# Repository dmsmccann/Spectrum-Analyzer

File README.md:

# W7ZOI Spectrum Analyzer

## KiCad Implementation with modifications by Andy McCann KA3KAF and Doug McCann KA3KAG

## Overview

This repository contains a complete KiCad implementation of the famous W7ZOI Spectrum Analyzer design, originally published in QST magazine. The W7ZOI spectrum analyzer is a well-regarded amateur radio test instrument design that provides a cost-effective solution for RF spectrum analysis.

## Project Description

The W7ZOI Spectrum Analyzer is a superheterodyne spectrum analyzer designed for amateur radio applications. It provides frequency analysis capabilities across the HF and VHF bands, making it an invaluable tool for antenna analysis, filter characterization, and general RF measurements.

### Key Features

- **Frequency Range**: Covers HF through VHF bands
- **Modular Design**: Hierarchical schematic organization for easy understanding and modification
- **Complete Implementation**: Includes all necessary subsystems:
  - VCO and 1st Mixer
  - 110 MHz / 7 MHz Filter sections
  - IF and Log Amplifier
  - 2nd Mixer and 2nd LO
  - Resolution Filters
  - Timebase circuitry
  - 15V Power Supply
  - 2dB Divider
  - 70 MHz Low-pass Filter

## Repository Structure

```text
├── hierarchical-schematic/     # Main hierarchical schematic files
├── 110mhz/                    # 110 MHz filter module
├── 15v-supply/                # Power supply module
├── 2db-div/                   # 2dB divider module
├── 2ndmixer-2ndlo/           # 2nd mixer and LO module
├── 70mhz-lpf/                # 70 MHz low-pass filter
├── 7mhz-crystal-oscillator/  # 7 MHz crystal oscillator
├── if-and-log-amp/           # IF and log amplifier
├── resolution-filters/        # Resolution filter bank
├── timebase/                 # Timebase generation
├── tracking-generator/        # Tracking generator module
├── vco-1stmixer/             # VCO and 1st mixer
├── literature/               # Reference documentation and articles
├── images/                   # Project images and diagrams
└── experimental-data/        # Test data and measurements
```

## Hardware Modules

### Core RF Path

- **VCO and 1st Mixer**: Frequency conversion front-end
- **110 MHz Filter**: First IF filtering
- **7 MHz Crystal Oscillator**: Local oscillator reference
- **2nd Mixer and LO**: Second frequency conversion
- **IF and Log Amplifier**: Signal conditioning and logarithmic response

### Support Circuits

- **15V Power Supply**: Clean, regulated power for all modules
- **Resolution Filters**: Selectable bandwidth filters
- **70 MHz Low-pass Filter**: Anti-aliasing and spurious suppression
- **2dB Divider**: Signal distribution
- **Timebase**: Sweep generation and timing

### Optional Modules

- **Tracking Generator**: Signal source for swept measurements
- **Two-tone Test**: Distortion analysis capability

## Documentation

The `literature/` directory contains extensive reference material including:

- Original QST articles (September 1998, November 1999, June 2001)
- Construction notes and updates
- Filter design references
- Technical papers on spectrum analysis
- Modification and improvement documentation

## Getting Started

### Prerequisites

- KiCad 6.0 or later
- Basic understanding of RF circuit design
- Amateur radio license (for legal operation)

### Opening the Project

1. Clone this repository
2. Open KiCad
3. Load the main project file: `hierarchical-schematic/W7ZOI Spectrum Analyzer.kicad_pro`

### Project Files

- **Schematic**: Hierarchical design with individual module schematics
- **PCB Layout**: Complete board layout for professional fabrication
- **3D Models**: Custom component models for visualization
- **BOM**: Bill of materials with part specifications

## Modifications and Improvements

This implementation includes several improvements over the original design:

- Updated component selections for current availability
- Improved PCB layout with better ground planes
- Enhanced power supply regulation
- Modernized connector choices
- Detailed silkscreen labeling

## Building the Analyzer

Refer to the documentation in the `literature/` directory for detailed construction information. The original QST articles provide comprehensive building instructions, alignment procedures, and performance specifications.

## Contributing

Contributions are welcome! Please feel free to submit issues, improvements, or additional documentation. When contributing:

1. Follow KiCad best practices for schematic and PCB design
2. Document any changes thoroughly
3. Test modifications before submitting
4. Update relevant documentation

## License

This project is based on the original W7ZOI design published in QST magazine. Please respect copyright and amateur radio regulations in your use of these designs.

## Authors and Acknowledgments

- **Original Design**: Wes Hayward (W7ZOI) and Terry White (VE3DTE)
- **KiCad Implementation**: Andy McCann (KA3KAF) and Doug McCann (KA3KAG)
- **Published in**: QST Magazine, September 1998 and subsequent articles

## References

- QST Magazine, September 1998: "A Spectrum Analyzer for the Radio Amateur"
- QST Magazine, November 1999: Part 2 and updates
- QST Magazine, June 2001: Additional modifications and tracking generator
- Various technical papers in the `literature/` directory

---

*This is an amateur radio project intended for educational and experimental use. Please ensure compliance with your local amateur radio regulations.*

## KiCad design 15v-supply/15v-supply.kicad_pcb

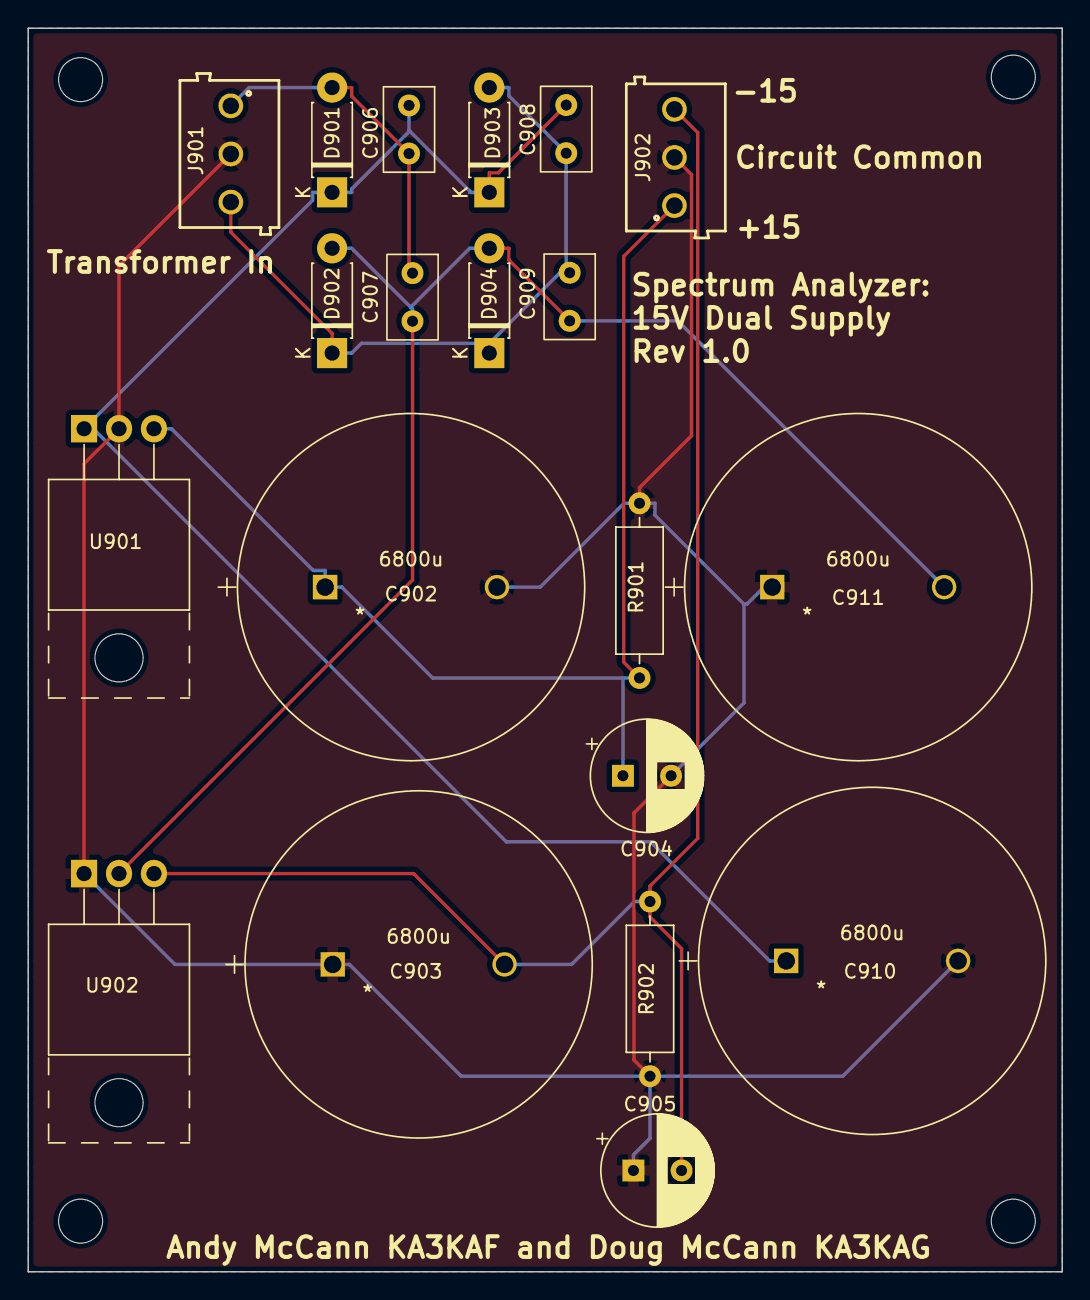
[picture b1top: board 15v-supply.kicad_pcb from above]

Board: 2 copper layers, 75.2 x 90.4 mm, 24 parts (0 on the bottom side), 7 nets.

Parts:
C902, C903, C910, C911: 6800u; 6800u-UVR1H682MRD6
C904, C905: 6.8u; CP_Radial_D8.0mm_P3.50mm
C906, C907, C908, C909: 0.01u; C_Rect_L6.0mm_W3.5mm_P3.5mm_QYX1H103JTP3TA
D901, D902, D903, D904: 1n5060; D_DO-41_SOD81_P7.62mm_Horizontal
H901, H902, H903, H905: MountingHole; MountingHole_3.2mm_M3
J901, J902: Terminal Block; terminal-block-691103110003
R901, R902: 2.2k; R_Axial_DIN0309_L9.0mm_D3.2mm_P12.70mm_Horizontal
U901: LM7815; TO-220-3_Horizontal_TabUp
U902: LM7915; TO-220-3_Horizontal_TabUp

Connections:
/7815 IN: C906.1, C908.1, C910.1, D901.1 (Cathode), D903.1 (Cathode), U901.1 (IN)
/7915 IN: C907.2, C909.2, C911.2, D902.2 (Anode), D904.2 (Anode), U902.2 (VI)
/+15 REGULATED: C902.1, C904.1, J902.1, R901.1, U901.3 (OUT)
/-15 REGULATED: C903.2, C905.2, J902.3, R902.2, U902.3 (VO)
/TRAN OUT1: C906.2, C907.1, D901.2 (Anode), J901.1
/TRAN OUT2: C908.2, C909.1, D902.1 (Cathode), D903.2 (Anode), D904.1 (Cathode), J901.3
GND: C902.2, C903.1, C904.2, C905.1, C910.2, C911.1, J901.2, J902.2, R901.2, R902.1, U901.2 (GND), U902.1 (GND)

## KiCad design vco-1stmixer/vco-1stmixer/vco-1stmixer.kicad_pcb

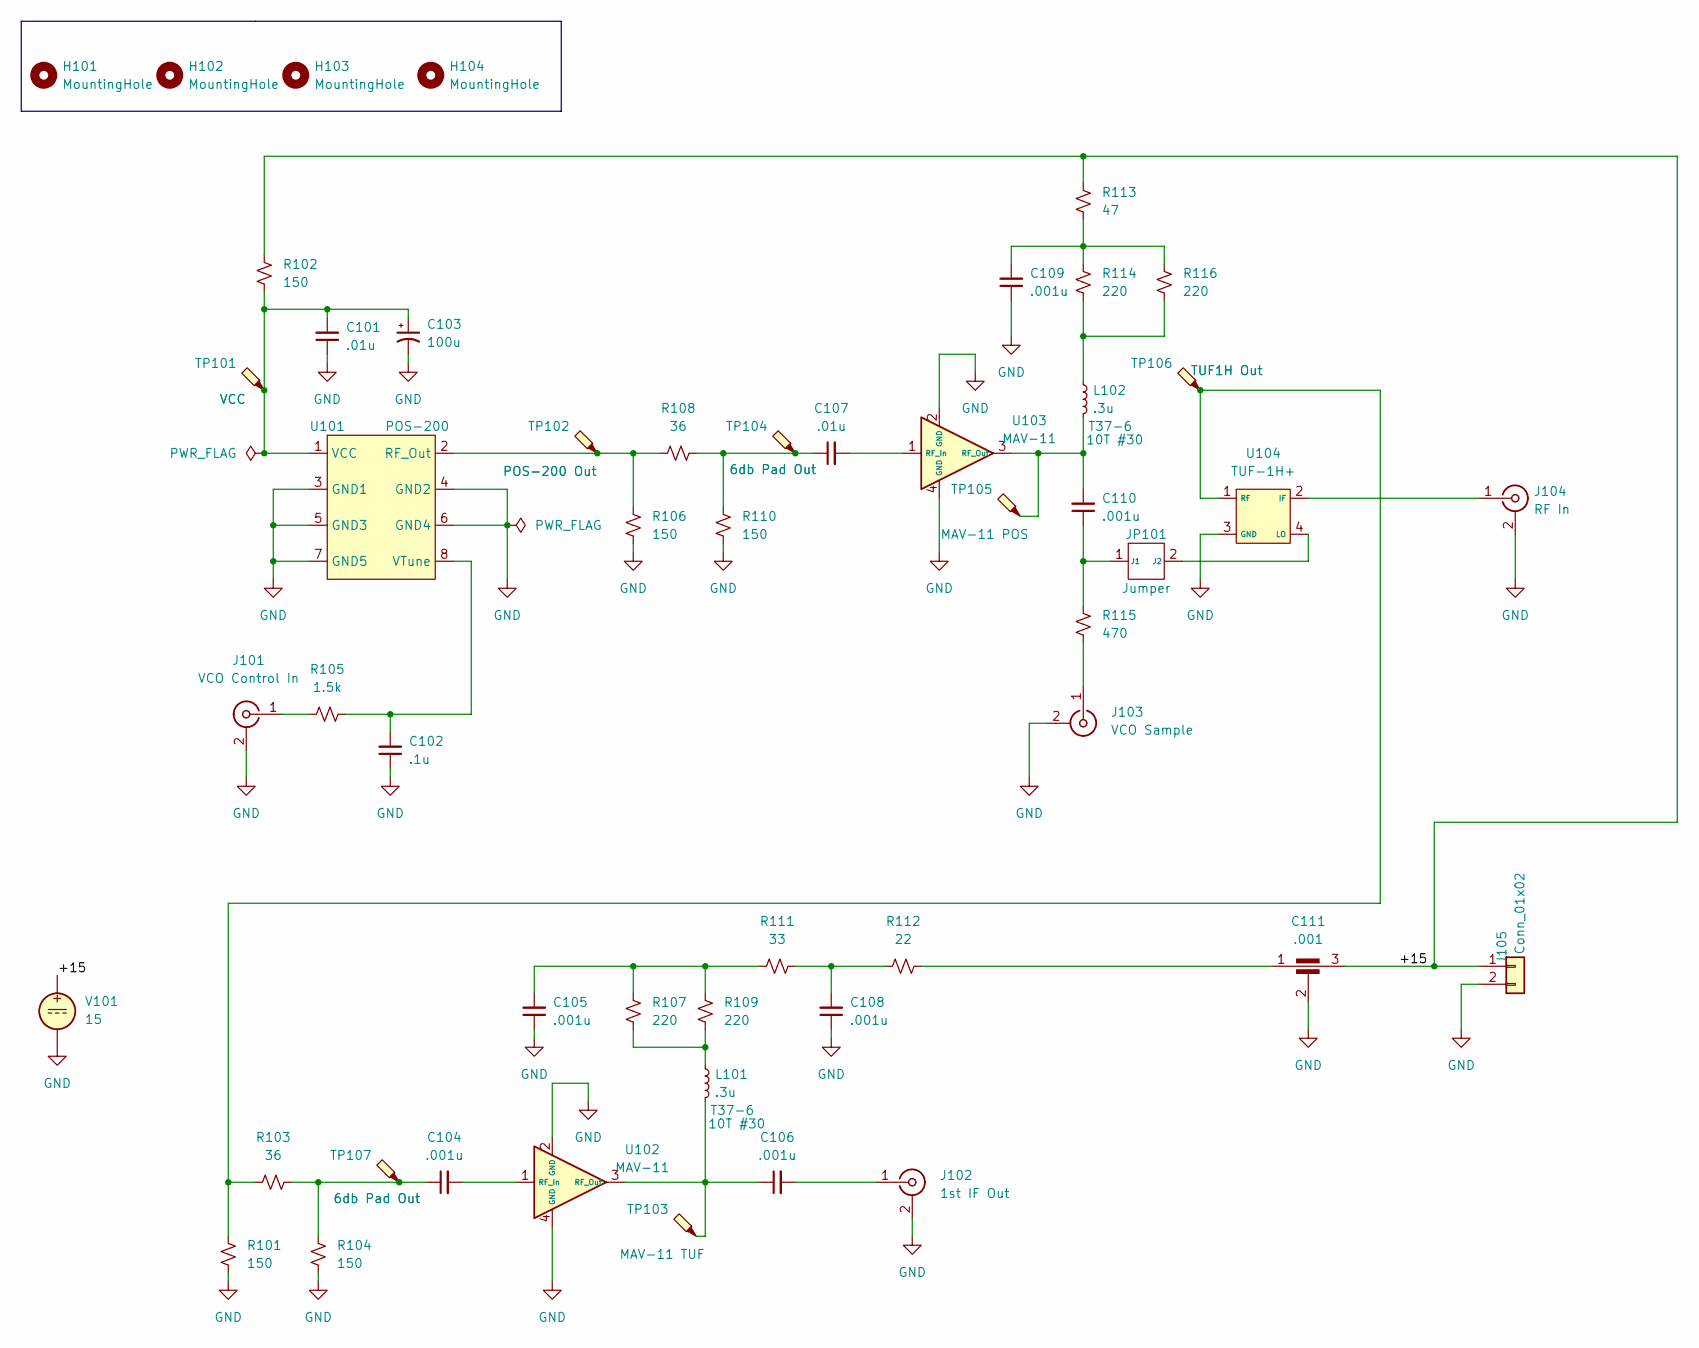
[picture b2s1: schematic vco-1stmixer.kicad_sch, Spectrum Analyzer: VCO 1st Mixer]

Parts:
C101, C107: .01u; C_Disc_D5.0mm_W2.5mm_P5.00mm
C102: .1u; C_Disc_D5.0mm_W2.5mm_P5.00mm
C103: 100u; CP_Radial_D8.0mm_P3.50mm
C104, C105, C106, C108, C109, C110: .001u; C_Disc_D5.0mm_W2.5mm_P5.00mm
C111: .001; DSS1N_MUR
H101, H102, H103, H104: MountingHole; MountingHole_3.2mm_M3
J101: VCO Control In; SolderWire-0.5sqmm_1x02_P4.6mm_D0.9mm_OD2.1mm
J102: 1st IF Out; SolderWire-0.5sqmm_1x02_P4.6mm_D0.9mm_OD2.1mm
J103: VCO Sample; PinHeader_1x02_P2.54mm_Vertical
J104: RF In; SolderWire-0.5sqmm_1x02_P4.6mm_D0.9mm_OD2.1mm
J105: Conn_01x02; SolderWire-0.5sqmm_1x02_P4.6mm_D0.9mm_OD2.1mm
JP101: Jumper; 22284028
L101, L102: .3u; L_Toroid_Vertical_L13.0mm_W6.5mm_P5.60mm
R101, R102, R104, R106, R110: 150; R_Axial_DIN0207_L6.3mm_D2.5mm_P7.62mm_Horizontal
R103, R108: 36; R_Axial_DIN0207_L6.3mm_D2.5mm_P7.62mm_Horizontal
R105: 1.5k; R_Axial_DIN0207_L6.3mm_D2.5mm_P7.62mm_Horizontal
R107, R109, R114, R116: 220; R_Axial_DIN0207_L6.3mm_D2.5mm_P7.62mm_Horizontal
R111: 33; R_Axial_DIN0207_L6.3mm_D2.5mm_P7.62mm_Horizontal
R112: 22; R_Axial_DIN0207_L6.3mm_D2.5mm_P7.62mm_Horizontal
R113: 47; R_Axial_DIN0207_L6.3mm_D2.5mm_P7.62mm_Horizontal
R115: 470; R_Axial_DIN0207_L6.3mm_D2.5mm_P7.62mm_Horizontal
TP101: VCC; TestPoint_Pad_1.0x1.0mm
TP102: POS-200 Out; TestPoint_Pad_1.0x1.0mm
TP103: MAV-11 TUF; TestPoint_Pad_1.0x1.0mm
TP104, TP107: 6db Pad Out; TestPoint_Pad_1.0x1.0mm
TP105: MAV-11 POS; TestPoint_Pad_1.0x1.0mm
TP106: TUF1H Out; TestPoint_Pad_1.0x1.0mm
U101: POS-200
U102, U103: MAV-11; MAV-11BSM&plus_
U104: TUF-1H+; TUF-1H
V101: 15

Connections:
/+15: C111.3, J105.1, R102.2, R113.2, V101.1
GND: C101.1, C102.1, C103.2, C105.1, C108.1, C109.1, C111.2, J101.2 (Ext), J102.2 (Ext), J103.2 (Ext), J104.2 (Ext), J105.2, R101.1, R104.1, R106.1, R110.1, U101.3 (GND1), U101.4 (GND2), U101.5 (GND3), U101.6 (GND4), U101.7 (GND5), U102.2 (GND), U102.4 (GND), U103.2 (GND), U103.4 (GND), U104.3 (GND), V101.2
unnamed: C104.1, R103.2, R104.2, TP107.1
unnamed: C105.2, R107.2, R109.2, R111.1
unnamed: C107.1, R108.2, R110.2, TP104.1
unnamed: C108.2, R111.2, R112.1
unnamed: C109.2, R113.1, R114.2, R116.2
unnamed: C111.1, R112.2
unnamed: J101.1 (In), R105.1
unnamed: C106.2, J102.1 (In)
unnamed: J103.1 (In), R115.1
unnamed: J104.1 (In), U104.2 (IF)
unnamed: C110.1, JP101.1 (J1), R115.2
unnamed: JP101.2 (J2), U104.4 (LO)
unnamed: L101.1, R107.1, R109.1
unnamed: L102.1, R114.1, R116.1
unnamed: R106.2, R108.1, TP102.1, U101.2 (RF_Out)
unnamed: C101.2, C103.1, R102.1, TP101.1, U101.1 (VCC)
unnamed: C102.2, R105.2, U101.8 (VTune)
unnamed: C104.2, U102.1 (RF_In)
unnamed: C106.1, L101.2, TP103.1, U102.3 (RF_Out)
unnamed: C107.2, U103.1 (RF_In)
unnamed: C110.2, L102.2, TP105.1, U103.3 (RF_Out)
unnamed: R101.2, R103.1, TP106.1, U104.1 (RF)

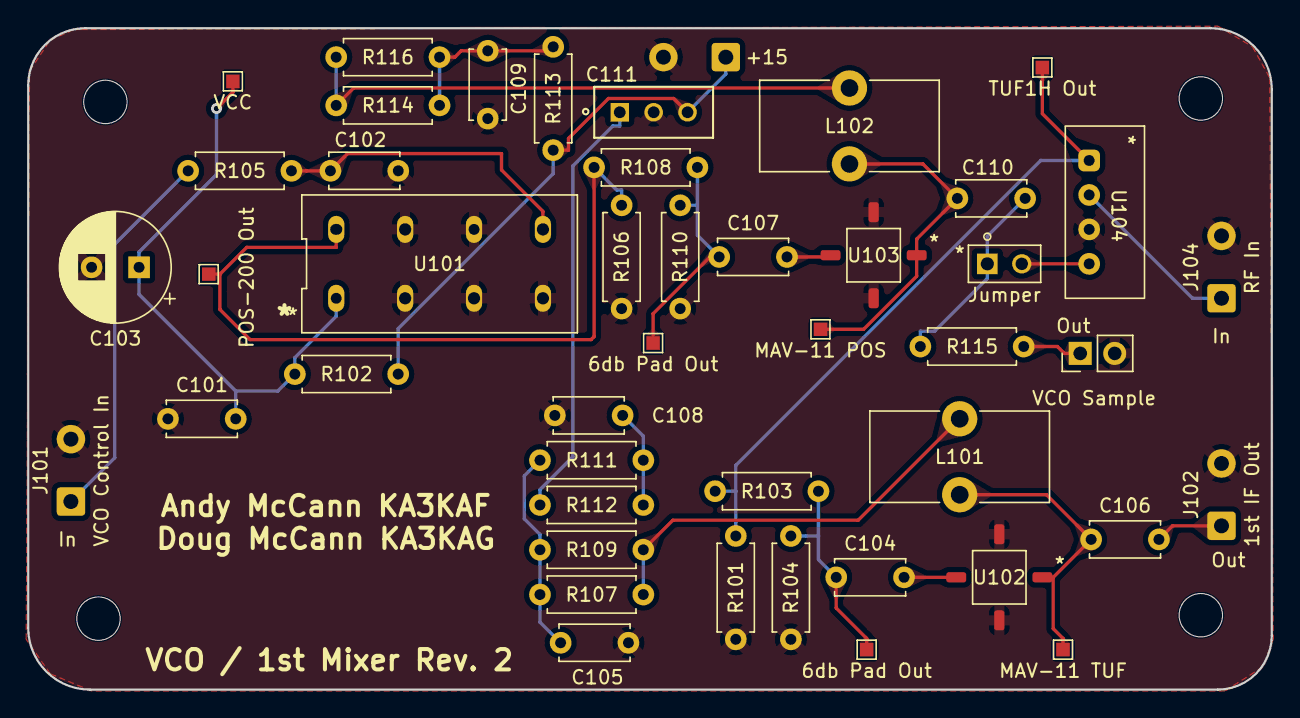
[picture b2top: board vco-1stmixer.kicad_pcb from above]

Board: 2 copper layers, 91.7 x 48.8 mm, 50 parts (0 on the bottom side), 24 nets.

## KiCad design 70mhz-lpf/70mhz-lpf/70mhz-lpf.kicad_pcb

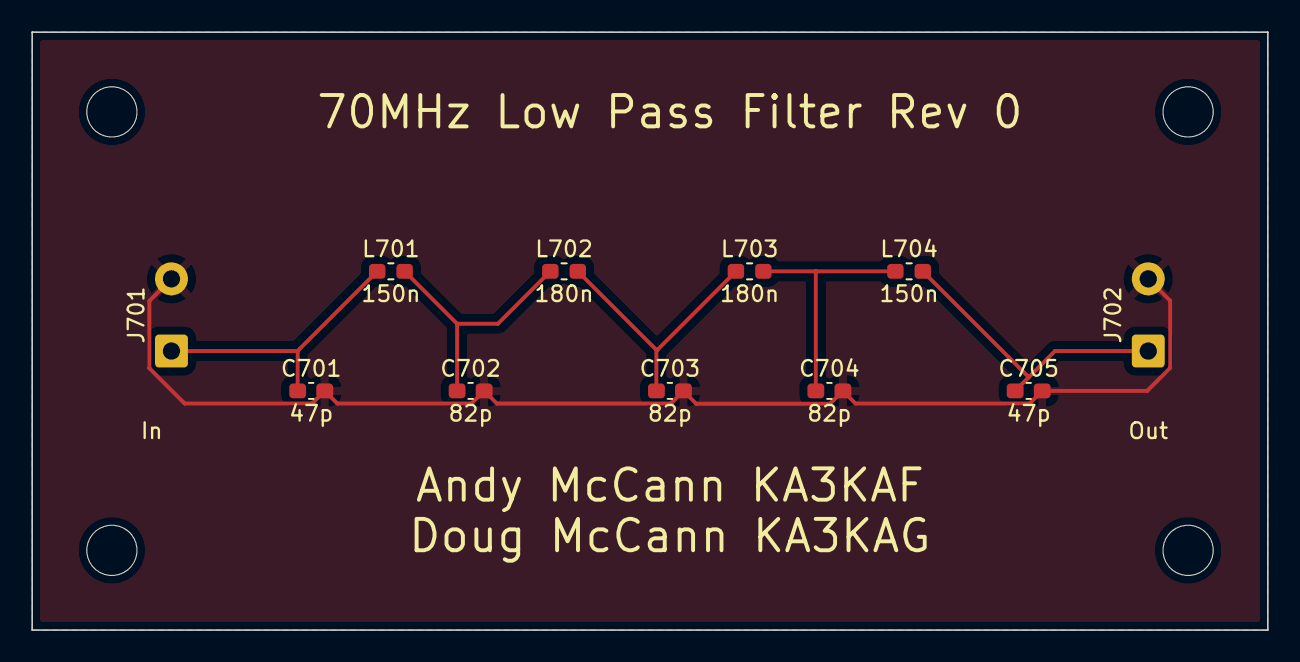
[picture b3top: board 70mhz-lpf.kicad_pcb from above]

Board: 2 copper layers, 78.7 x 38.1 mm, 15 parts (0 on the bottom side), 6 nets.

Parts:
C701, C705: 47p; C_0603_1608Metric_Pad1.08x0.95mm_HandSolder
C702, C703, C704: 82p; C_0603_1608Metric_Pad1.08x0.95mm_HandSolder
H701, H702, H703, H704: MountingHole; MountingHole_3.2mm_M3
J701, J702: Coax Solder Point; SolderWire-0.5sqmm_1x02_P4.6mm_D0.9mm_OD2.1mm
L701, L704: 150n; L_0603_1608Metric_Pad1.05x0.95mm_HandSolder
L702, L703: 180n; L_0603_1608Metric_Pad1.05x0.95mm_HandSolder

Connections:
/In: C701.1, J701.1 (In), L701.1
/Out: C705.1, J702.1 (In), L704.2
GND: C701.2, C702.2, C703.2, C704.2, C705.2, J701.2 (Ext), J702.2 (Ext)
unnamed: C702.1, L701.2, L702.1
unnamed: C703.1, L702.2, L703.1
unnamed: C704.1, L703.2, L704.1

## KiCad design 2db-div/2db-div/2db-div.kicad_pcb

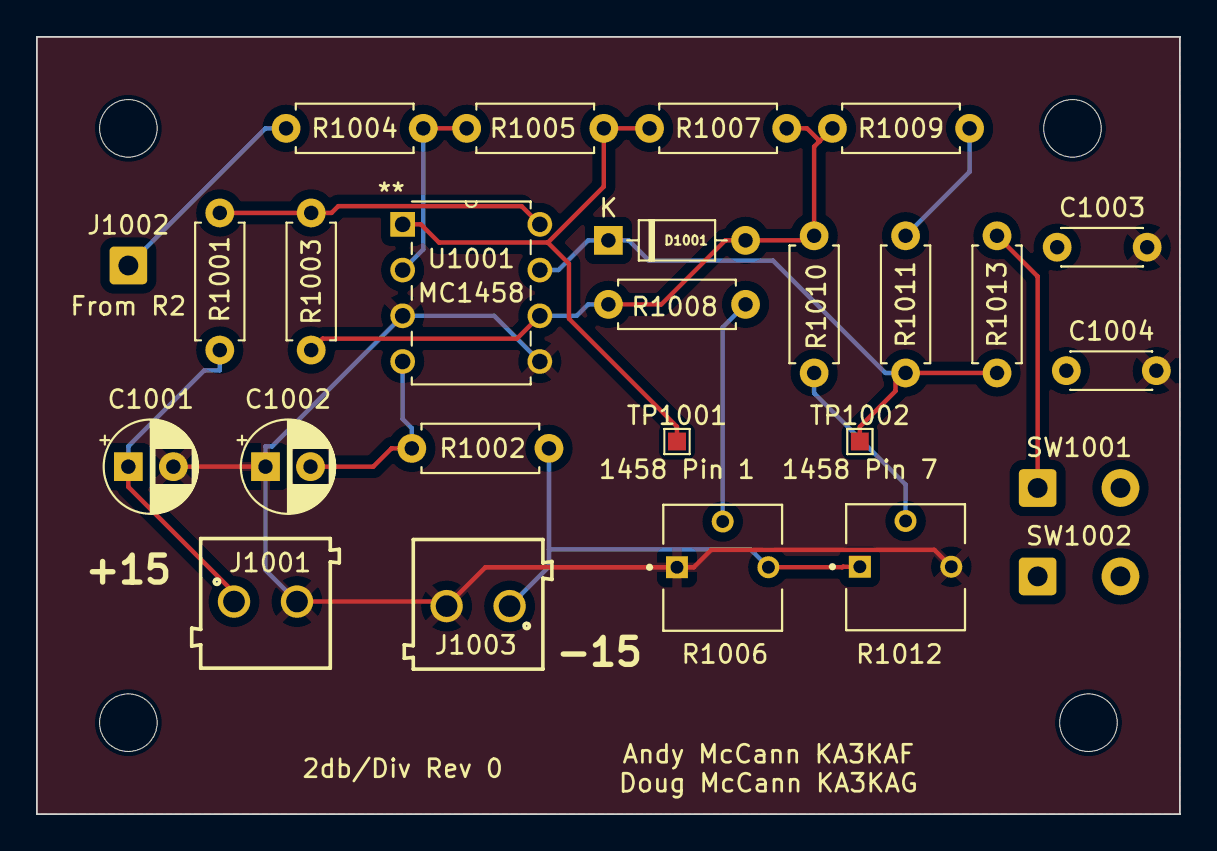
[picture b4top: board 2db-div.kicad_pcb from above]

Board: 2 copper layers, 63.5 x 43.2 mm, 30 parts (0 on the bottom side), 16 nets.

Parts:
C1001, C1002: 100u; CP_Radial_D5.0mm_P2.50mm
C1003: .1u; C_Disc_D4.3mm_W1.9mm_P5.00mm
C1004: 3.3u; C_Disc_D4.3mm_W1.9mm_P5.00mm
D1001: 1N4148; D_DO-35_SOD27_P7.62mm_Horizontal
H1001, H1002, H1003, H1004: type="R" model="MountingHole" lib=""; MountingHole_3.2mm_M3
J1001, J1003: Conn_01x02; 691103110002
J1002: From R2; SolderWire-0.5sqmm_1x01_D0.9mm_OD2.1mm
R1001, R1002: 43; R_Axial_DIN0207_L6.3mm_D2.5mm_P7.62mm_Horizontal
R1003, R1004, R1008, R1009: 20k; R_Axial_DIN0207_L6.3mm_D2.5mm_P7.62mm_Horizontal
R1005: 40k; R_Axial_DIN0207_L6.3mm_D2.5mm_P7.62mm_Horizontal
R1006, R1012: 10k; TRIM_3362P-1-103LF
R1007: 10k; R_Axial_DIN0207_L6.3mm_D2.5mm_P7.62mm_Horizontal
R1010: 249k; R_Axial_DIN0207_L6.3mm_D2.5mm_P7.62mm_Horizontal
R1011: 4.99k; R_Axial_DIN0207_L6.3mm_D2.5mm_P7.62mm_Horizontal
R1013: 1k; R_Axial_DIN0207_L6.3mm_D2.5mm_P7.62mm_Horizontal
SW1001: 2dB; SolderWire-0.5sqmm_1x02_P4.6mm_D0.9mm_OD2.1mm
SW1002: type="R" model="Video" lib=""; SolderWire-0.5sqmm_1x02_P4.6mm_D0.9mm_OD2.1mm
TP1001: 1458 Pin 1; TestPoint_Pad_1.0x1.0mm
TP1002: 1458 Pin 7; TestPoint_Pad_1.0x1.0mm
U1001: MC1458; MC1458P

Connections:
/+15: C1001.1, J1001.1, R1001.2
/-15: J1003.1, R1002.1, R1006.3, R1012.1
/In: J1002.1, R1004.1
GND: C1001.2, C1002.1, C1003.2, C1004.2, J1001.2, J1003.2, R1006.1, R1012.3, U1001.3 (+), U1001.5 (+)
unnamed: C1003.1, SW1002.2
unnamed: C1004.1, SW1002.1
unnamed: D1001.2 (A), R1003.1, R1007.2, R1008.2, R1009.1, R1010.1, U1001.6 (-)
unnamed: D1001.1 (K), R1011.2, R1013.1, TP1002.1, U1001.7
unnamed: R1005.2, R1007.1, TP1001.1, U1001.1
unnamed: R1006.2, R1008.1
unnamed: R1009.2, R1011.1
unnamed: R1010.2, R1012.2
unnamed: R1013.2, SW1001.1 (A)
unnamed: R1004.2, R1005.1, U1001.2 (-)
unnamed: R1001.1, R1003.2, U1001.8 (V+)
unnamed: C1002.2, R1002.2, U1001.4 (V-)

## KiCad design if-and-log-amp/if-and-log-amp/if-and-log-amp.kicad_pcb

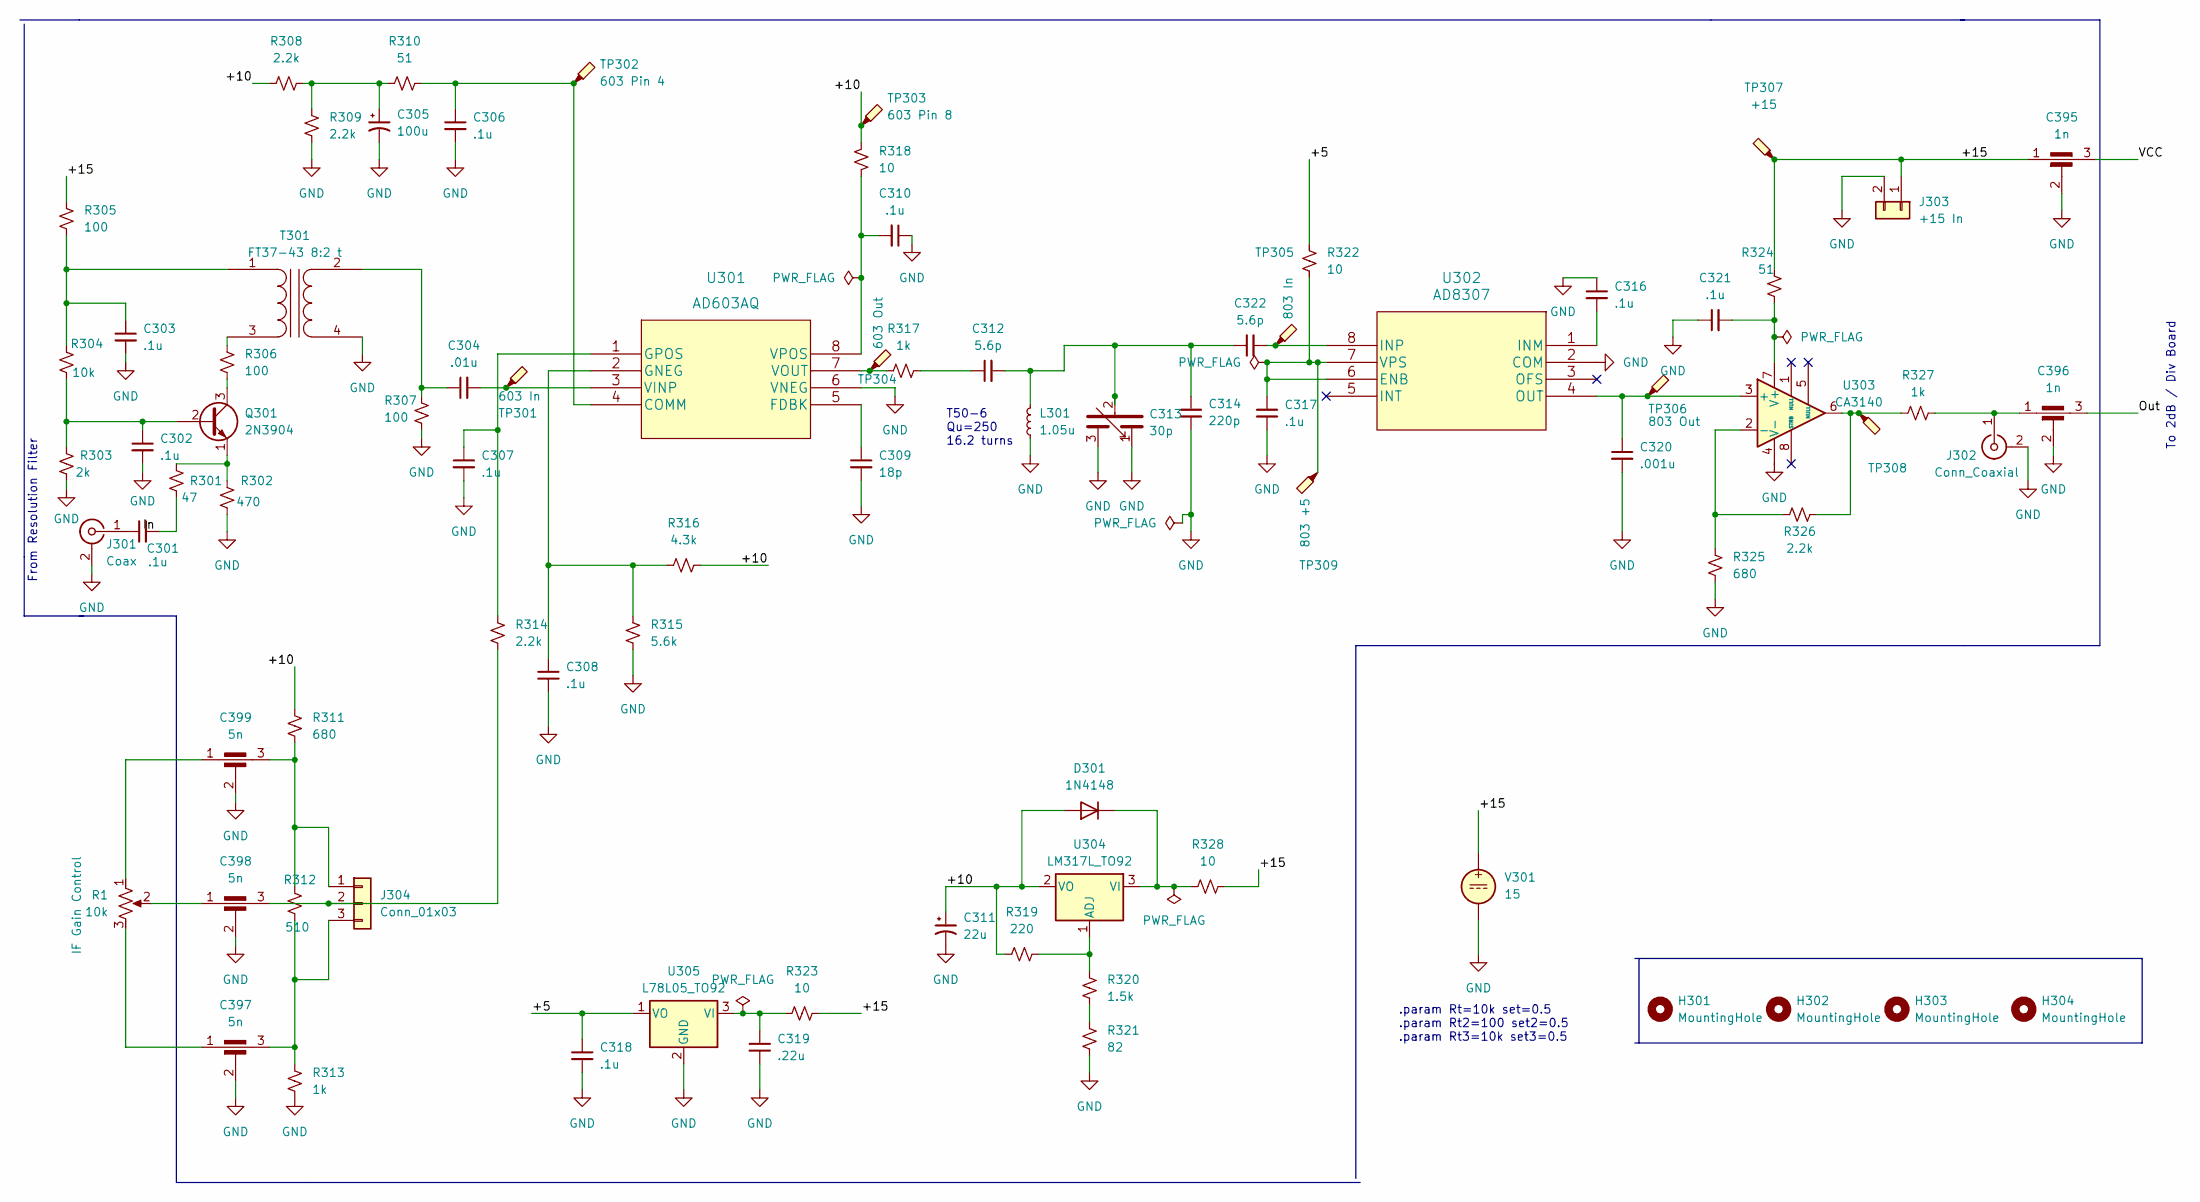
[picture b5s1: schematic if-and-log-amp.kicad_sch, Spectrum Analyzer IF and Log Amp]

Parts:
C301, C302, C303, C306, C307, C308, C310, C316, C317, C318, C321: .1u; C_Disc_D5.0mm_W2.5mm_P5.00mm
C304: .01u; C_Disc_D5.0mm_W2.5mm_P5.00mm
C305: 100u; CP_Radial_D5.0mm_P2.50mm
C309: 18p; C_Disc_D5.0mm_W2.5mm_P5.00mm
C311: 22u; CP_Radial_D5.0mm_P2.50mm
C312, C322: 5.6p; C_Disc_D5.0mm_W2.5mm_P5.00mm
C313: 30p; BFC280831659
C314: 220p; C_Disc_D5.0mm_W2.5mm_P5.00mm
C319: .22u; C_Disc_D5.0mm_W2.5mm_P5.00mm
C320: .001u; C_Disc_D5.0mm_W2.5mm_P5.00mm
C395, C396: 1n; DSS1NB32A102Q91A
C397, C398, C399: 5n; DSS1NB32A102Q91A
D301: 1N4148; D_DO-35_SOD27_P7.62mm_Horizontal
H301, H302, H303, H304: MountingHole; MountingHole_3.2mm_M3
J301: Coax; SolderWire-0.5sqmm_1x02_P4.6mm_D0.9mm_OD2.1mm
J302: Conn_Coaxial; SolderWire-0.5sqmm_1x02_P4.6mm_D0.9mm_OD2.1mm
J303: +15 In; 691103110002
J304: Conn_01x03; SolderWire-0.5sqmm_1x03_P4.6mm_D0.9mm_OD2.1mm
L301: 1.05u; L_Toroid_Vertical_L13.0mm_W6.5mm_P5.60mm
Q301: 2N3904; TO-92_Inline
R1: 10k
R301: 47; R_Axial_DIN0207_L6.3mm_D2.5mm_P7.62mm_Horizontal
R302: 470; R_Axial_DIN0207_L6.3mm_D2.5mm_P7.62mm_Horizontal
R303: 2k; R_Axial_DIN0207_L6.3mm_D2.5mm_P7.62mm_Horizontal
R304: 10k; R_Axial_DIN0207_L6.3mm_D2.5mm_P7.62mm_Horizontal
R305, R306, R307: 100; R_Axial_DIN0207_L6.3mm_D2.5mm_P7.62mm_Horizontal
R308, R309, R314, R326: 2.2k; R_Axial_DIN0207_L6.3mm_D2.5mm_P7.62mm_Horizontal
R310, R324: 51; R_Axial_DIN0207_L6.3mm_D2.5mm_P7.62mm_Horizontal
R311, R325: 680; R_Axial_DIN0207_L6.3mm_D2.5mm_P7.62mm_Horizontal
R312: 510; R_Axial_DIN0207_L6.3mm_D2.5mm_P7.62mm_Horizontal
R313, R317, R327: 1k; R_Axial_DIN0207_L6.3mm_D2.5mm_P7.62mm_Horizontal
R315: 5.6k; R_Axial_DIN0207_L6.3mm_D2.5mm_P7.62mm_Horizontal
R316: 4.3k; R_Axial_DIN0207_L6.3mm_D2.5mm_P7.62mm_Horizontal
R318, R322, R323, R328: 10; R_Axial_DIN0207_L6.3mm_D2.5mm_P7.62mm_Horizontal
R319: 220; R_Axial_DIN0207_L6.3mm_D2.5mm_P7.62mm_Horizontal
R320: 1.5k; R_Axial_DIN0207_L6.3mm_D2.5mm_P7.62mm_Horizontal
R321: 82; R_Axial_DIN0207_L6.3mm_D2.5mm_P7.62mm_Horizontal
T301: FT37-43 8:2 t; Transformer Vertical 1P 1S
TP301: 603 In; TestPoint_Pad_1.0x1.0mm
TP302: 603 Pin 4; TestPoint_Pad_1.0x1.0mm
TP303: 603 Pin 8; TestPoint_Pad_1.0x1.0mm
TP304: 603 Out; TestPoint_Pad_1.0x1.0mm
TP305: 803 In; TestPoint_Pad_1.0x1.0mm
TP306: 803 Out; TestPoint_Pad_1.0x1.0mm
TP307: +15; TestPoint_Pad_1.0x1.0mm
TP308: CA3140 Out; TestPoint_Pad_1.0x1.0mm
TP309: 803 +5; TestPoint_Pad_1.0x1.0mm
U301: AD603AQ
U302: AD8307; AD8307AN
U303: CA3140; CA3140EZ
U304: LM317L_TO92; TO-92_Inline
U305: L78L05_TO92; TO-92_Inline
V301: 15

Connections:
/+5: C318.1, R322.1, U305.1 (VO)
/+10: C311.1, D301.2 (A), R308.1, R311.1, R316.2, R318.1, R319.1, TP303.1, U304.2 (VO)
/+15: C395.1, J303.1, R305.1, R323.1, R324.2, R328.2, TP307.1, V301.1
GND: C302.2, C303.2, C305.2, C306.2, C307.2, C308.2, C309.2, C310.1, C311.2, C313.1, C313.3, C314.2, C316.1, C317.2, C318.2, C319.2, C320.2, C321.1, C395.2, C396.2, C397.2, C398.2, C399.2, J301.2 (Ext), J302.2 (Ext), J303.2, L301.1, R302.2, R303.2, R307.2, R309.2, R313.2, R315.2, R321.2, R325.2, T301.4 (SA), U301.6 (VNEG), U302.2 (COM), U303.4 (V-), U305.2 (GND), V301.2
unnamed: C301.2, R301.2
unnamed: C305.1, R308.2, R309.1, R310.1
unnamed: C312.1, R317.2
unnamed: C312.2, C313.2, C314.1, C322.1, L301.2
unnamed: C397.1, R1.3
unnamed: C398.1, R1.2
unnamed: C399.1, R1.1
unnamed: D301.1 (K), R328.1, U304.3 (VI)
unnamed: C301.1, J301.1 (In)
unnamed: C396.1, J302.1 (In), R327.2
unnamed: C399.3, J304.1, R311.2, R312.1
unnamed: C398.3, J304.2, R314.2
unnamed: C397.3, J304.3, R312.2, R313.1
unnamed: C302.1, Q301.2 (B), R303.1, R304.2
unnamed: Q301.3 (C), R306.2
unnamed: Q301.1 (E), R301.1, R302.1
unnamed: R320.2, R321.1
unnamed: R326.1, R327.1, TP308.1, U303.6
unnamed: C303.1, R304.1, R305.2, T301.1 (AA)
unnamed: R306.1, T301.3 (AB)
unnamed: C304.1, R307.1, T301.2 (SB)
unnamed: C306.1, R310.2, TP302.1, U301.4 (COMM)
unnamed: C309.1, U301.5 (FDBK)
unnamed: C308.1, R315.1, R316.1, U301.2 (GNEG)
unnamed: C307.1, R314.1, U301.1 (GPOS)
unnamed: C304.2, TP301.1, U301.3 (VINP)
unnamed: R317.1, TP304.1, U301.7 (VOUT)
unnamed: C310.2, R318.2, U301.8 (VPOS)
unnamed: C317.1, R322.2, TP309.1, U302.6 (ENB), U302.7 (VPS)
unnamed: C316.2, U302.1 (INM)
unnamed: C322.2, TP305.1, U302.8 (INP)
unnamed: C320.1, TP306.1, U302.4 (OUT), U303.3 (+)
unnamed: R325.1, R326.2, U303.2 (-)
unnamed: C321.2, R324.1, U303.7 (V+)
unnamed: R319.2, R320.1, U304.1 (ADJ)
unnamed: C319.1, R323.2, U305.3 (VI)

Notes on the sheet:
T50-6 Qu=250 16.2 turns
From Resolution Filter
To 2dB / Div Board
.param Rt=10k set=0.5 .param Rt2=100 set2=0.5 .param Rt3=10k set3=0.5

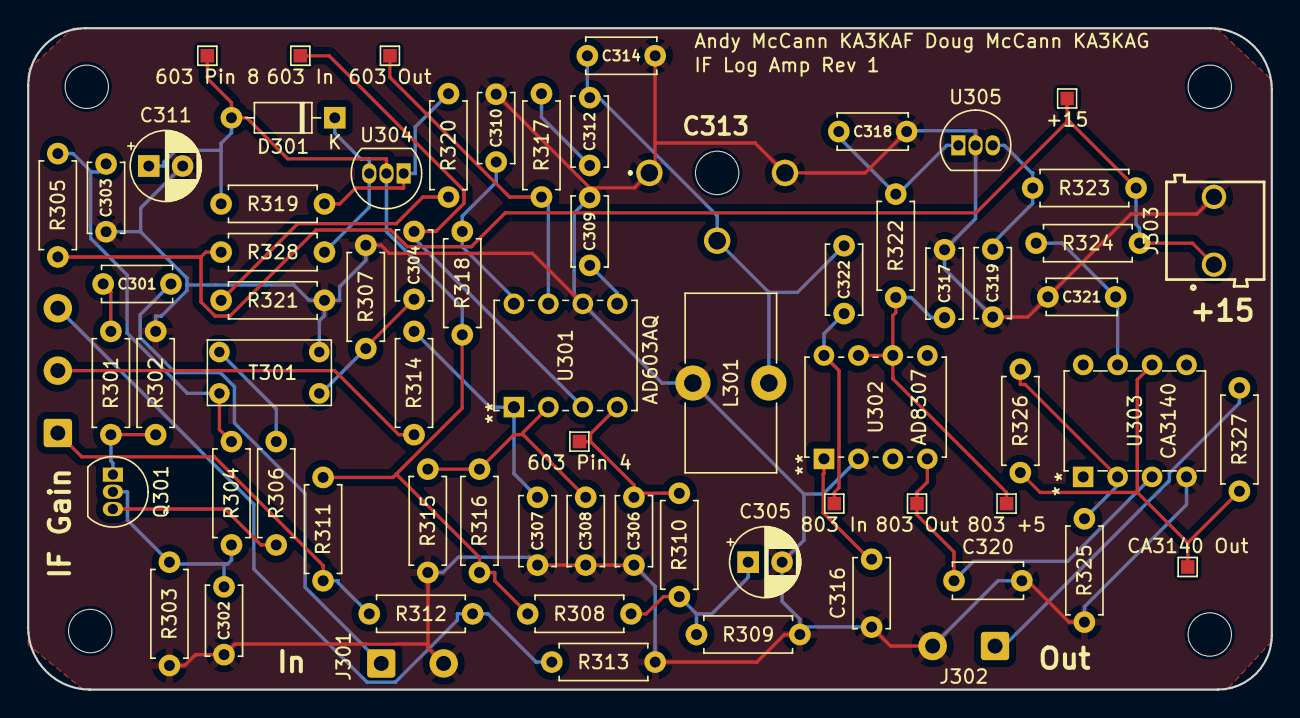
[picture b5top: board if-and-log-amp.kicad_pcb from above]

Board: 2 copper layers, 91.7 x 48.8 mm, 75 parts (0 on the bottom side), 37 nets.

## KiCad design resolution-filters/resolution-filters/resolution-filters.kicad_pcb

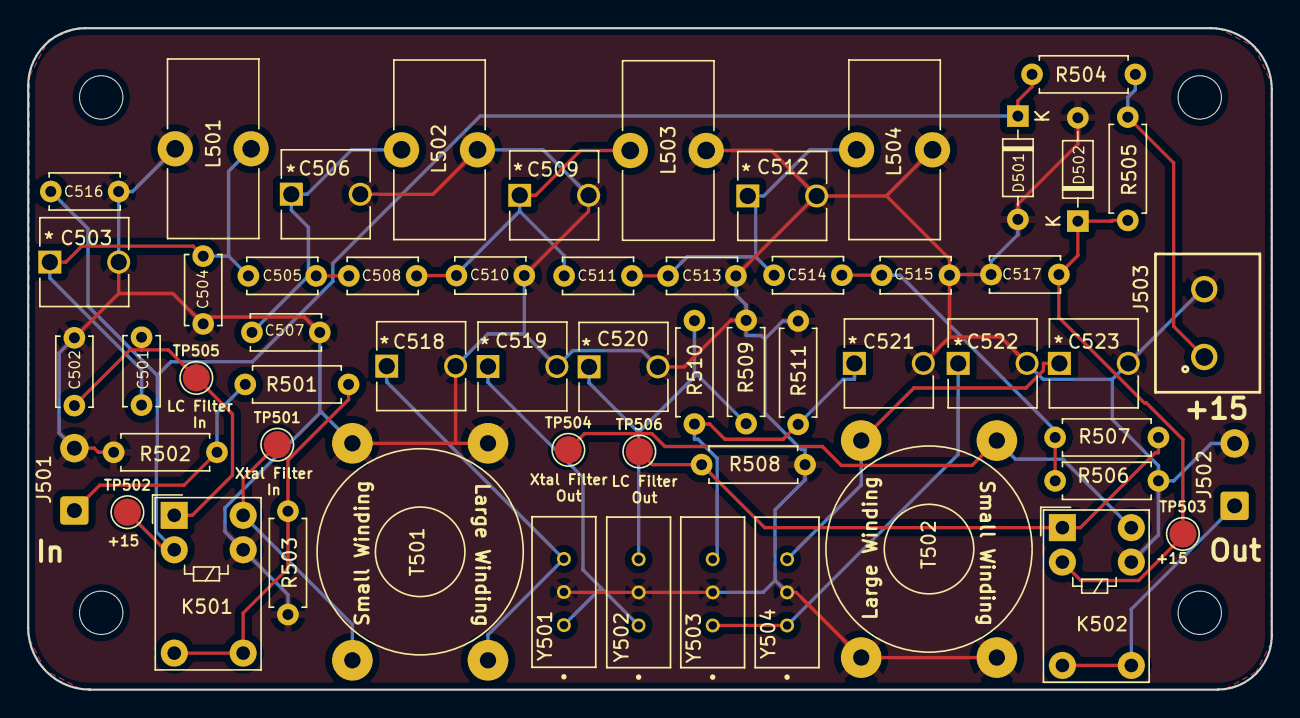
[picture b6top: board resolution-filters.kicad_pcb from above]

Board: 2 copper layers, 91.7 x 48.8 mm, 61 parts (0 on the bottom side), 22 nets.

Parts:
C501, C514: 56p; C_Disc_D5.0mm_W2.5mm_P5.00mm
C502, C515: 120p; C_Disc_D5.0mm_W2.5mm_P5.00mm
C503, C506, C509, C512: 12p-60p; GKG60015
C504, C513: 100p; C_Disc_D5.0mm_W2.5mm_P5.00mm
C505, C511: 5.6p; C_Disc_D5.0mm_W2.5mm_P5.00mm
C507, C510: 150p; C_Disc_D5.0mm_W2.5mm_P5.00mm
C508: 3.3p; C_Disc_D5.0mm_W2.5mm_P5.00mm
C516, C517: .1u; C_Disc_D5.0mm_W2.5mm_P5.00mm
C518, C519, C520, C521, C522, C523: 1.8p-10p; GKG60015
D501, D502: 1N4148; D_DO-35_SOD27_P7.62mm_Horizontal
H501, H502, H503, H504: MountingHole; MountingHole_3.2mm_M3
J501, J502: Conn_Coaxial; SolderWire-0.5sqmm_1x02_P4.6mm_D0.9mm_OD2.1mm
J503: Terminal Block; 691137710002
K501, K502: G5V-1; Relay_SPDT_Omron_G5V-1
L501, L502, L503, L504: 1.15u; L_Toroid_Vertical_L13.0mm_W6.5mm_P5.60mm
R501: 36; R_Axial_DIN0207_L6.3mm_D2.5mm_P7.62mm_Horizontal
R502, R503: 150; R_Axial_DIN0207_L6.3mm_D2.5mm_P7.62mm_Horizontal
R504, R505: 270; R_Axial_DIN0207_L6.3mm_D2.5mm_P7.62mm_Horizontal
R506, R508: 10M; R_Axial_DIN0207_L6.3mm_D2.5mm_P7.62mm_Horizontal
R507: 0; R_Axial_DIN0207_L6.3mm_D2.5mm_P7.62mm_Horizontal
R509, R511: 9.1k; R_Axial_DIN0207_L6.3mm_D2.5mm_P7.62mm_Horizontal
R510: 2.2k; R_Axial_DIN0207_L6.3mm_D2.5mm_P7.62mm_Horizontal
T501, T502: Transformer_1P_1S; Transformer_Toroid_Horizontal_D14.0mm_Amidon-T50
TP501, TP502, TP503, TP504, TP505, TP506: TestPoint; TestPoint_Pad_D2.0mm
Y501, Y502, Y503, Y504: 10.7MHz; XTAL_ECS-10.7-7.5B

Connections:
/30Khz Out: K502.10, T502.2 (AA), TP504.1
/30kHz In: K501.10, T501.2 (AA), TP501.1
/300kHz In: C501.1, C502.1, K501.1, TP505.1
/300kHz Out: K502.1, R507.2, R508.1, TP506.1
/501-in: C516.1, D501.1 (K), K501.2, R504.1, TP502.1
/502-in: C517.1, D502.1 (K), K502.2, R505.2, TP503.1
/VIn: J501.1 (In), R501.1, R502.1
GND: C502.2, C503.2, C504.2, C506.2, C507.2, C509.2, C510.2, C512.2, C513.2, C515.2, C516.2, C517.2, C518.2, C519.2, C520.2, C521.2, C522.2, C523.2, D501.2 (A), D502.2 (A), J501.2 (Ext), J502.2 (Ext), J503.2, K501.9, K502.9, L501.2, L502.2, L503.2, L504.2, R502.2, R503.2, R506.2, R508.2, R509.2, R511.2, T501.1 (AB), T501.3 (SA), T502.1 (AB), T502.3 (SA), Y501.2, Y502.2, Y503.2, Y504.2
unnamed: C501.2, C503.1, C504.1, C505.1, L501.1
unnamed: C505.2, C506.1, C507.1, C508.1, L502.1
unnamed: C508.2, C509.1, C510.1, C511.1, L503.1
unnamed: C511.2, C512.1, C513.1, C514.1, L504.1
unnamed: C514.2, C515.1, R506.1, R507.1
unnamed: C518.1, T501.4 (SB), Y501.3
unnamed: C519.1, Y501.1, Y502.1
unnamed: C520.1, R509.1, R510.1, Y502.3
unnamed: C521.1, R510.2, R511.1, Y503.3
unnamed: C522.1, Y503.1, Y504.1
unnamed: C523.1, T502.4 (SB), Y504.3
unnamed: J503.1, R504.2, R505.1
unnamed: J502.1 (In), K502.5, K502.6
unnamed: K501.5, K501.6, R501.2, R503.1

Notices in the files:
parts and their libraries:
Copyright 2021 Accelerated Designs. All rights reserved.
